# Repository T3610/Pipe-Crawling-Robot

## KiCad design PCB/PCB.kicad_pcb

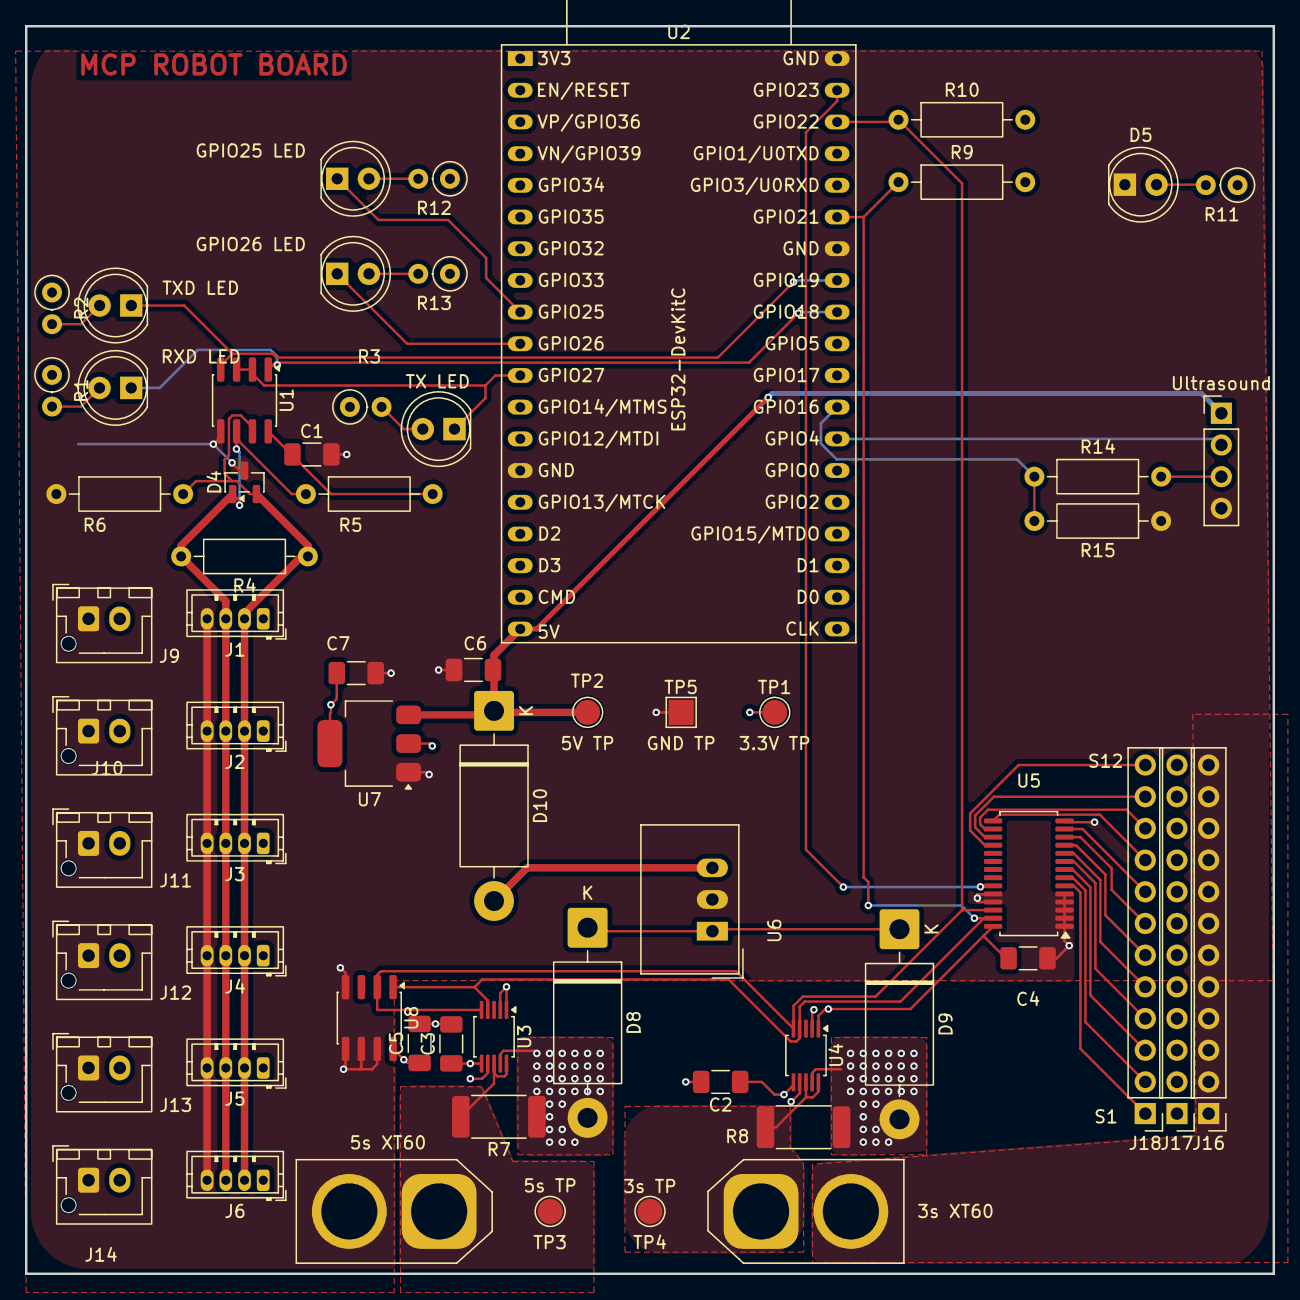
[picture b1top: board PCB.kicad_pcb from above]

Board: 4 copper layers, 100.0 x 100.0 mm, 63 parts (0 on the bottom side), 40 nets.

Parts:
3s XT60, 5s XT60: Conn_01x02; AMASS_XT60-M_1x02_P7.20mm_Vertical
C1, C2, C3, C4, C5: 100n; C_1206_3216Metric_Pad1.33x1.80mm_HandSolder
C6, C7: 10u; C_1206_3216Metric_Pad1.33x1.80mm_HandSolder
D4: SM712_SOT23; SOT-23
D5: LED; LED_D5.0mm
D8, D9, D10: 1N5822; D_DO-201AD_P15.24mm_Horizontal
GPIO25 LED, GPIO26 LED: LED; LED_D5.0mm
J1, J2, J3, J4, J5, J6: Conn_01x04; JST_ZH_B4B-ZR_1x04_P1.50mm_Vertical
J9, J10, J11, J12, J13, J14: Conn_01x02; JST_XH_B2B-XH-AM_1x02_P2.50mm_Vertical
J16, J17, J18: Conn_01x12; PinHeader_1x12_P2.54mm_Vertical
R1, R2, R3: 1000; R_Axial_DIN0207_L6.3mm_D2.5mm_P2.54mm_Vertical
R4: 120; R_Axial_DIN0207_L6.3mm_D2.5mm_P10.16mm_Horizontal
R5, R6, R9, R10: 4k7; R_Axial_DIN0207_L6.3mm_D2.5mm_P10.16mm_Horizontal
R7, R8: 2m; R_2512_6332Metric_Pad1.40x3.35mm_HandSolder
R11, R12, R13: 300; R_Axial_DIN0207_L6.3mm_D2.5mm_P2.54mm_Vertical
R14: 1000; R_Axial_DIN0207_L6.3mm_D2.5mm_P10.16mm_Horizontal
R15: 2200; R_Axial_DIN0207_L6.3mm_D2.5mm_P10.16mm_Horizontal
RXD LED: LED; LED_D5.0mm
TP1: 3.3V TP; TestPoint_Pad_D2.0mm
TP2: 5V TP; TestPoint_Pad_D2.0mm
TP3: 5s TP; TestPoint_Pad_D2.0mm
TP4: 3s TP; TestPoint_Pad_D2.0mm
TP5: GND TP; TestPoint_Pad_2.0x2.0mm
TX LED: LED; LED_D5.0mm
TXD LED: LED; LED_D5.0mm
U1: MAX3485; SOIC-8_3.9x4.9mm_P1.27mm
U2: ESP32-DevKitC
U3, U4: INA226; TSSOP-10_3x3mm_P0.5mm
U5: PCA9685PW; TSSOP-28_4.4x9.7mm_P0.65mm
U6: TSR_1-2450; Converter_DCDC_TRACO_TSR-1_THT
U7: AMS1117-3.3; SOT-223-3_TabPin2
U8: LM75B; SOIC-8_3.9x4.9mm_P1.27mm
Ultrasound: Conn_01x04; PinHeader_1x04_P2.54mm_Vertical

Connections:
+3V3: C1.1, C2.1, C3.1, C4.1, C5.1, C7.1, R1.1, R2.1, R3.1, R5.2, R9.2, R10.2, R11.1, R12.1, R13.1, TP1.1 (1_1), U1.8 (VCC), U3.1 (A1), U3.2 (A0), U3.6 (VS), U4.1 (A1), U4.6 (VS), U5.28 (VDD), U7.2 (VO), U8.8 (+Vs)
+3s_LIPO: D9.2 (A), J17.1, J17.2, J17.3, J17.4, J17.5, J17.6, J17.7, J17.8, J17.9, J17.10, J17.11, J17.12, R8.1, U4.9 (Vin-)
+3s_LIPO_EXT: 3s XT60.1, R8.2, TP4.1 (1_1), U4.8 (Vbus), U4.10 (Vin+)
+5V: C6.1, D10.1 (K), TP2.1 (1_1), U2.19 (5V), U7.3 (VI), Ultrasound.1
+5s_LIPO: D8.2 (A), J9.2, J10.2, J11.2, J12.2, J13.2, J14.2, R7.1, U3.9 (Vin-)
+5s_LIPO_EXT: 5s XT60.1, R7.2, TP3.1 (1_1), U3.8 (Vbus), U3.10 (Vin+)
/485_N: D4.2 (A2), J1.2, J2.2, J3.2, J4.2, J5.2, J6.2, R4.1, R6.2, U1.7 (B)
/485_P: D4.1 (A1), J1.3, J2.3, J3.3, J4.3, J5.3, J6.3, R4.2, R5.1, U1.6 (A)
/RXD_485: RXD LED.1 (K), U1.1 (RO), U2.30 (GPIO18)
/SCL: R10.1, U2.36 (GPIO22), U3.5 (SCL), U4.5 (SCL), U5.26 (SCL), U8.2 (SCL)
/SDA: R9.1, U2.33 (GPIO21), U3.4 (SDA), U4.4 (SDA), U5.27 (SDA), U8.1 (SDA)
/SERVO_1: J18.1, U5.6 (LED0)
/SERVO_2: J18.2, U5.7 (LED1)
/SERVO_3: J18.3, U5.8 (LED2)
/SERVO_4: J18.4, U5.9 (LED3)
/SERVO_5: J18.5, U5.10 (LED4)
/SERVO_6: J18.6, U5.11 (LED5)
/SERVO_7: J18.7, U5.12 (LED6)
/SERVO_8: J18.8, U5.13 (LED7)
/SERVO_9: J18.9, U5.15 (LED8)
/SERVO_10: J18.10, U5.16 (LED9)
/SERVO_11: J18.11, U5.17 (LED10)
/SERVO_12: J18.12, U5.18 (LED11)
/SERVO_EN: U2.37 (GPIO23), U5.23 (~OE)
/STAT_LED_1: GPIO25 LED.1 (K), U2.9 (DAC_1/ADC2_CH8/GPIO25)
/STAT_LED_2: GPIO26 LED.1 (K), U2.10 (DAC_2/ADC2_CH9/GPIO26)
/TXD_485: TXD LED.1 (K), U1.4 (DI), U2.31 (GPIO19)
/TX_485_EN: TX LED.1 (K), U1.2 (~RE), U1.3 (DE), U2.11 (ADC2_CH7/GPIO27)
/US_ECHO: R14.1, R15.2, U2.27 (GPIO16)
/US_TRIG: U2.26 (ADC2_CH0/GPIO4), Ultrasound.2
GND: 3s XT60.2, 5s XT60.2, C1.2, C2.2, C3.2, C4.2, C5.2, C6.2, C7.2, D4.3 (common), D5.1 (K), J1.4, J2.4, J3.4, J4.4, J5.4, J6.4, J9.1, J10.1, J11.1, J12.1, J13.1, J14.1, J16.1, J16.2, J16.3, J16.4, J16.5, J16.6, J16.7, J16.8, J16.9, J16.10, J16.11, J16.12, R6.1, R15.1, TP5.1 (1_1), U1.5 (GND), U2.14 (GND), U2.32 (GND), U2.38 (GND), U3.7 (GND), U4.2 (A0), U4.7 (GND), U5.1 (A0), U5.2 (A1), U5.3 (A2), U5.4 (A3), U5.5 (A4), U5.14 (VSS), U5.24 (A5), U5.25 (EXTCLK), U6.2 (GND), U7.1 (GND), U8.4 (GND), U8.5 (A2), U8.6 (A1), U8.7 (A0), Ultrasound.4
unnamed: R1.2, RXD LED.2 (A)
unnamed: R2.2, TXD LED.2 (A)
unnamed: R3.2, TX LED.2 (A)
unnamed: D5.2 (A), R11.2
unnamed: GPIO25 LED.2 (A), R12.2
unnamed: GPIO26 LED.2 (A), R13.2
unnamed: D8.1 (K), D9.1 (K), U6.1 (Vin)
unnamed: D10.2 (A), U6.3 (Vout)
unnamed: R14.2, Ultrasound.3
